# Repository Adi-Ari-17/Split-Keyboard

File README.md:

# Split-Keyboard

This is my first time building a full keyboard, although I have built a macropad before. It is a split keyboard, and I am building it to test out connection between two microcontrollers.

## PCB

This is my PCB for the keyboard, in this photo it is disconnected so I can make the case around it in onshpae.

I know it looks a little messy but I plan on the case being not a thing layer just covering it and acctually giving it a shape.

This is the schmatic for my PCB I used this as a parent page so I can just copy the two halves of the keyboard.

This is one of the pages, the left side, but both are identical

This the 3d view (it is still not connected)

## CAD

I worked on my CAD two seperate times the first time I had the PCB connected and I couldn't figure out a good way to split it so I made a base model

After I splitted it in Kicad I made my case. I paticularly like this design it looks minamilistic, but it also looks kinda unique. 

 I used a little help from my friend to make this cause I'm not the best at CAD. :) 

 I also had to make to seperate models cause each of my keyboard sides are different. (heh)

 ## Code

 I just used the Zmk method and watched some out of date videos for this one
 I used a bit of Claude for debugging and finding out what I should plug in where.
 I also used AI for the keymaps since it is a lot of repeating work

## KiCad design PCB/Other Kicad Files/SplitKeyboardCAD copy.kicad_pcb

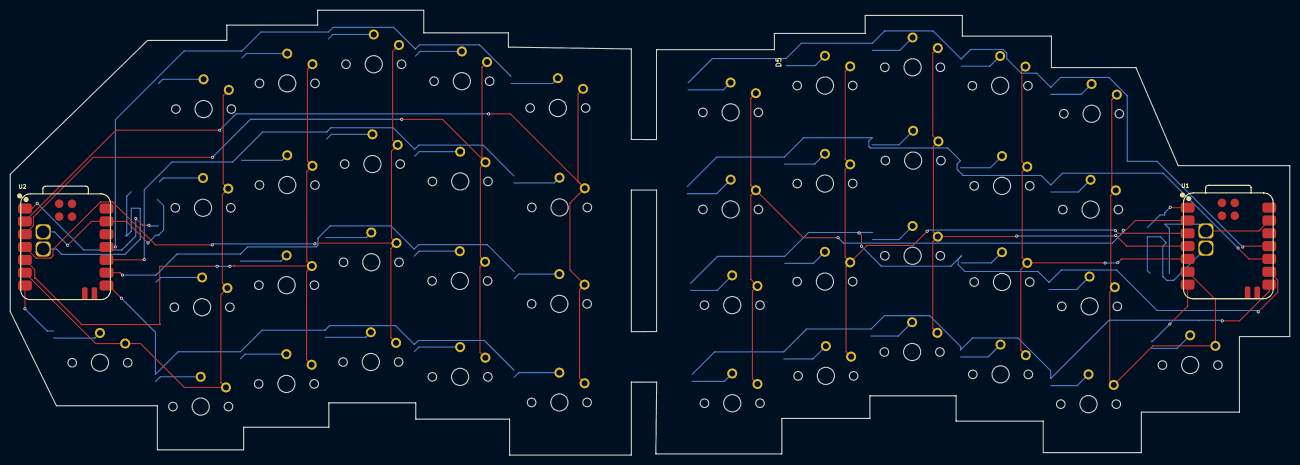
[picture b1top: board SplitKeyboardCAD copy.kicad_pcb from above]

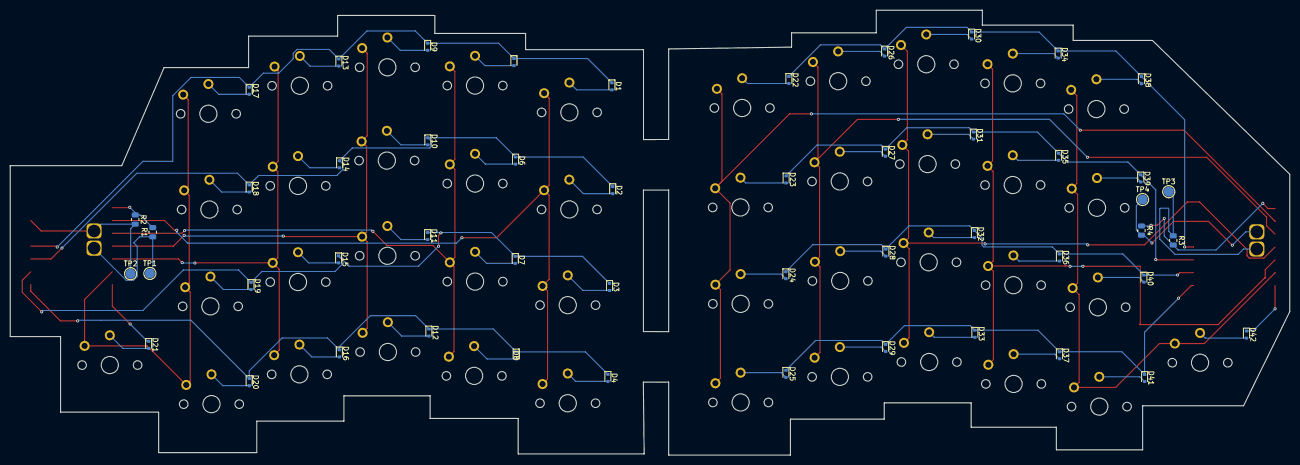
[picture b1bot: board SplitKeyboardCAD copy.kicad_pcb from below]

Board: 2 copper layers, 253.5 x 88.1 mm, 94 parts (50 on the bottom side), 55 nets.

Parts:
D1, D2, D3, D4, D5, D6, D7, D8, D9, D10, D11, D12, D13, D14, D15, D16, D17, D18, D19, D20, D21, D22, D23, D24, D25, D26, D27, D28, D29, D30, D31, D32, D33, D34, D35, D36, D37, D38, D39, D40, D41, D42: 1N4148WT; D_SOD-523
R1, R3: 806k; R_0805_2012Metric
R2, R4: 2M; R_0805_2012Metric
SW1, SW2, SW3, SW4, SW5, SW6, SW7, SW8, SW9, SW10, SW11, SW12, SW13, SW14, SW15, SW16, SW17, SW18, SW19, SW20, SW21, SW22, SW23, SW24, SW25, SW26, SW27, SW28, SW29, SW30, SW31, SW32, SW33, SW34, SW35, SW36, SW37, SW38, SW39, SW40, SW41, SW42: SW_Push; SW_choc_v1_1.75u
TP1, TP3: BAT; TestPoint_Pad_D2.0mm
TP2, TP4: GND; TestPoint_Pad_D2.0mm
U1, U2: XIAO-nRF52840-SMD; modified-XIAO-nRF52840-SMD

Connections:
BT_PIN: R1.2, R2.1, R3.2, R4.1, U1.1 (P0.02_A0_D0), U2.1 (P0.02_A0_D0)
Column0: SW1.1, SW2.1, SW3.1, SW4.1, SW22.1, SW23.1, SW24.1, SW25.1, U1.2 (P0.03_A1_D1), U2.2 (P0.03_A1_D1)
Column1: SW5.1, SW6.1, SW7.1, SW8.1, SW26.1, SW27.1, SW28.1, SW29.1, U1.3 (P0.28_A2_D2), U2.3 (P0.28_A2_D2)
Column2: SW9.1, SW10.1, SW11.1, SW12.1, SW30.1, SW31.1, SW32.1, SW33.1, U1.4 (P0.29_A3_D3), U2.4 (P0.29_A3_D3)
Column3: SW13.1, SW14.1, SW15.1, SW16.1, SW34.1, SW35.1, SW36.1, SW37.1, U1.5 (P0.04_A4_D4_SDA), U2.5 (P0.04_A4_D4_SDA)
Column4: SW17.1, SW18.1, SW19.1, SW20.1, SW21.1, SW38.1, SW39.1, SW40.1, SW41.1, SW42.1, U1.6 (P0.05_A5_D5_SCL), U2.6 (P0.05_A5_D5_SCL)
GND: R2.2, R4.2, TP2.1, TP4.1, U1.13 (GND), U1.16 (GND), U2.13 (GND), U2.16 (GND)
unnamed: D1.2 (A), SW1.2
unnamed: D2.2 (A), SW2.2
unnamed: D3.2 (A), SW3.2
unnamed: D4.2 (A), SW4.2
unnamed: D5.2 (A), SW5.2
unnamed: D6.2 (A), SW6.2
unnamed: D7.2 (A), SW7.2
unnamed: D8.2 (A), SW8.2
unnamed: D9.2 (A), SW9.2
unnamed: D10.2 (A), SW10.2
unnamed: D11.2 (A), SW11.2
unnamed: D12.2 (A), SW12.2
unnamed: D13.2 (A), SW13.2
unnamed: D14.2 (A), SW14.2
unnamed: D15.2 (A), SW15.2
unnamed: D16.2 (A), SW16.2
unnamed: D17.2 (A), SW17.2
unnamed: D18.2 (A), SW18.2
unnamed: D19.2 (A), SW19.2
unnamed: D20.2 (A), SW20.2
unnamed: D21.2 (A), SW21.2
unnamed: D22.2 (A), SW22.2
unnamed: D23.2 (A), SW23.2
unnamed: D24.2 (A), SW24.2
unnamed: D25.2 (A), SW25.2
unnamed: D26.2 (A), SW26.2
unnamed: D27.2 (A), SW27.2
unnamed: D28.2 (A), SW28.2
unnamed: D29.2 (A), SW29.2
unnamed: D30.2 (A), SW30.2
unnamed: D31.2 (A), SW31.2
unnamed: D32.2 (A), SW32.2
unnamed: D33.2 (A), SW33.2
unnamed: D34.2 (A), SW34.2
unnamed: D35.2 (A), SW35.2
unnamed: D36.2 (A), SW36.2
unnamed: D37.2 (A), SW37.2
unnamed: D38.2 (A), SW38.2
unnamed: D39.2 (A), SW39.2
unnamed: D40.2 (A), SW40.2
unnamed: D41.2 (A), SW41.2
unnamed: D42.2 (A), SW42.2
Row0: D1.1 (K), D5.1 (K), D9.1 (K), D13.1 (K), D17.1 (K), D22.1 (K), D26.1 (K), D30.1 (K), D34.1 (K), D38.1 (K), U1.11 (P1.15_D10_MOSI), U2.11 (P1.15_D10_MOSI)
Row1: D2.1 (K), D6.1 (K), D10.1 (K), D14.1 (K), D18.1 (K), D23.1 (K), D27.1 (K), D31.1 (K), D35.1 (K), D39.1 (K), U1.10 (P1.14_D9_MISO), U2.10 (P1.14_D9_MISO)
Row2: D3.1 (K), D7.1 (K), D11.1 (K), D15.1 (K), D19.1 (K), D24.1 (K), D28.1 (K), D32.1 (K), D36.1 (K), D40.1 (K), U1.9 (P1.13_D8_SCK), U2.9 (P1.13_D8_SCK)
Row3: D4.1 (K), D8.1 (K), D12.1 (K), D16.1 (K), D20.1 (K), D25.1 (K), D29.1 (K), D33.1 (K), D37.1 (K), D41.1 (K), U1.8 (P1.12_D7_RX), U2.8 (P1.12_D7_RX)
Row4: D21.1 (K), D42.1 (K), U1.7 (P1.11_D6_TX), U2.7 (P1.11_D6_TX)
VBAT: R1.1, R3.1, TP1.1, TP3.1, U1.15 (BAT), U2.15 (BAT)

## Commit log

2026-04-09 Add PCB files
2026-04-09 Add exported PCB and CAD files
2026-04-18 Update files before push
2026-04-18 Remove embedded repo ZMK-configeration from index
2026-04-19 Added Uf2 Files to the ZMK code section#
